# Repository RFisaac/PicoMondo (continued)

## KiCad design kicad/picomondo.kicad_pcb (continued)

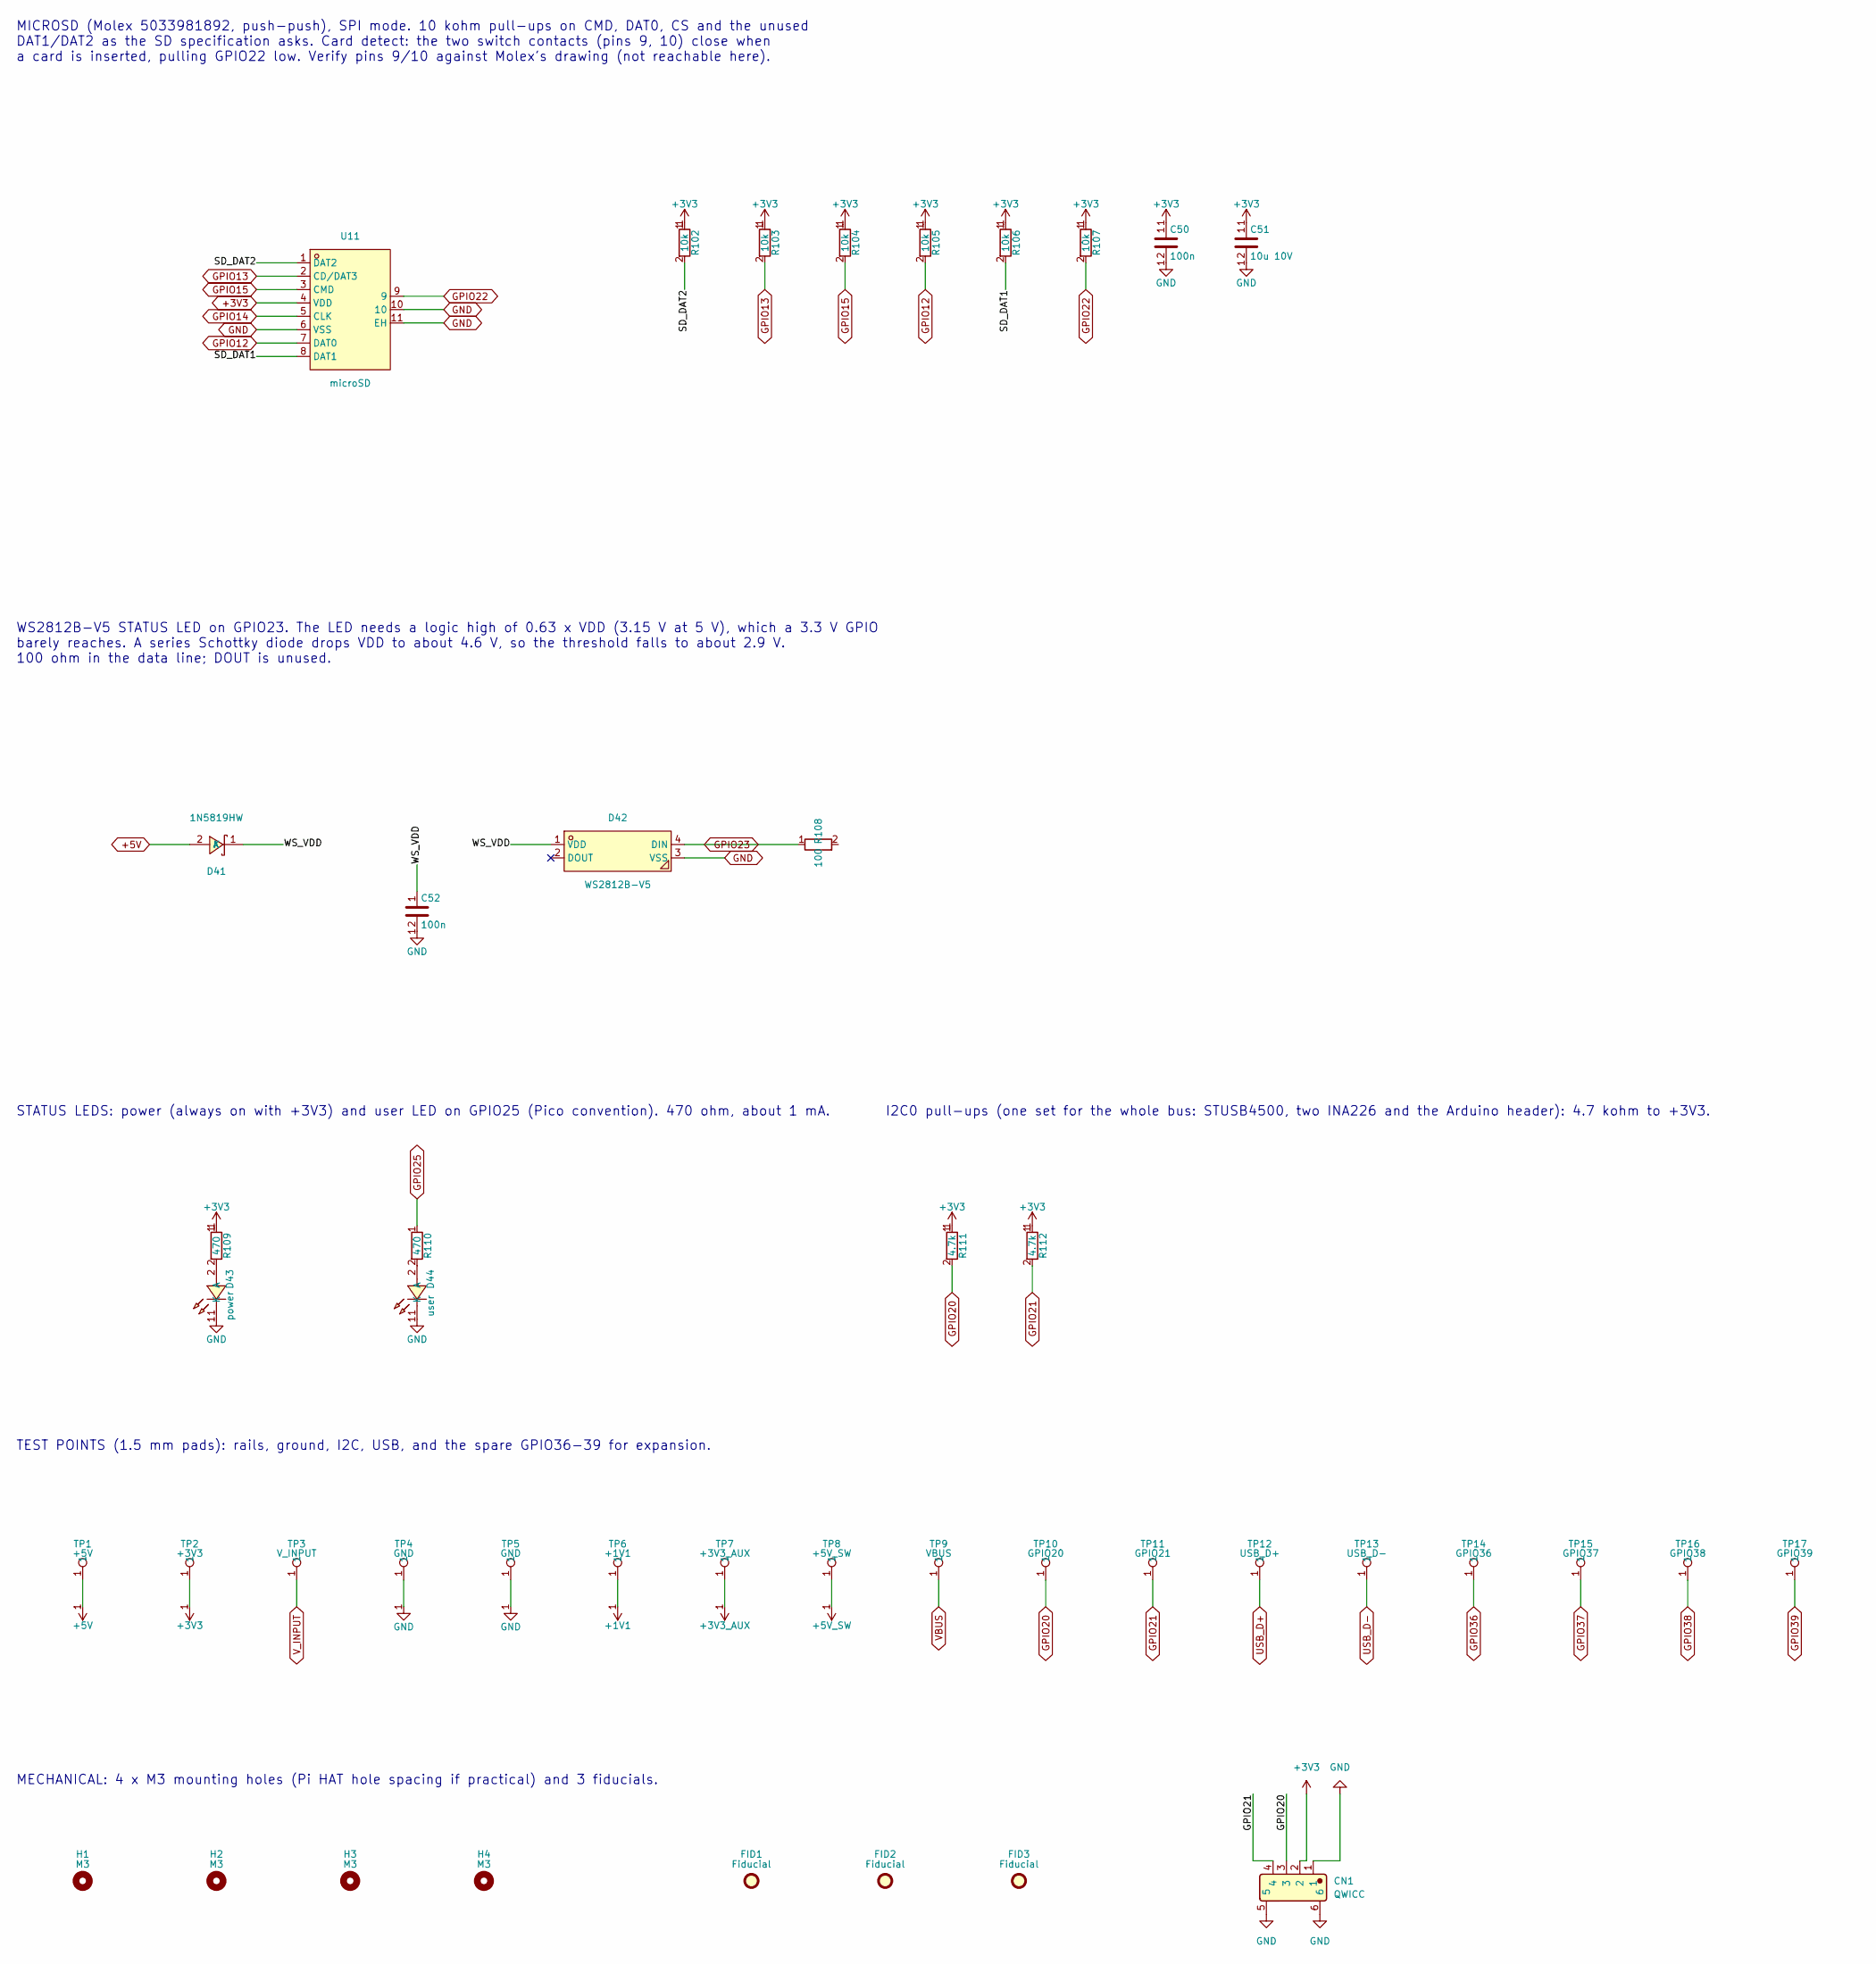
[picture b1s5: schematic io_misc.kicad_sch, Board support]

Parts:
C50, C52: 100n; C_0402_1005Metric; MPN CL05B104KB54PNC; LCSC C307331
C51: 10u 10V; C_0805_2012Metric; MPN CL21A106KAYNNNE; LCSC C15850
CN1: QWICC; XY-SM04B-SRSS-TB; Manufacturer Part XY-SM04B-SRSS-TB; LCSC C51940130
D41: 1N5819HW; SOD-123_L2.7-W1.6-LS3.7-RD; MPN 1N5819HW-7-F; LCSC C82544
D42: WS2812B-V5; LED-SMD_4P-L5.0-W5.0-LS5.4-TL-1; MPN WS2812B-V5/W; LCSC C2874885
D43: power; LED-SMD_L1.0-W0.5-RD_WHITE; MPN LW QH8G-Q2OO-3K5L-1; LCSC C7220928
D44: user; LED-SMD_L1.0-W0.5-RD_WHITE; MPN LW QH8G-Q2OO-3K5L-1; LCSC C7220928
FID1, FID2, FID3: Fiducial; Fiducial_1mm_Mask2mm
H1, H2, H3, H4: M3; MountingHole_3.2mm_M3
R102, R103, R104, R105, R106, R107: 10k; R_0402_1005Metric; MPN 0402WGF1002TCE; LCSC C25744
R108: 100; R_0402_1005Metric; MPN 0402WGF1000TCE; LCSC C25076
R109, R110: 470; R_0402_1005Metric; MPN 0402WGF4700TCE; LCSC C25117
R111, R112: 4.7k; R_0402_1005Metric; MPN 0402WGF4701TCE; LCSC C25900
TP1: +5V; TestPoint_Pad_D1.5mm
TP2: +3V3; TestPoint_Pad_D1.5mm
TP3: V_INPUT; TestPoint_Pad_D1.5mm
TP4, TP5: GND; TestPoint_Pad_D1.5mm
TP6: +1V1; TestPoint_Pad_D1.5mm
TP7: +3V3_AUX; TestPoint_Pad_D1.5mm
TP8: +5V_SW; TestPoint_Pad_D1.5mm
TP9: VBUS; TestPoint_Pad_D1.5mm
TP10: GPIO20; TestPoint_Pad_D1.5mm
TP11: GPIO21; TestPoint_Pad_D1.5mm
TP12: USB_D+; TestPoint_Pad_D1.5mm
TP13: USB_D-; TestPoint_Pad_D1.5mm
TP14: GPIO36; TestPoint_Pad_D1.5mm
TP15: GPIO37; TestPoint_Pad_D1.5mm
TP16: GPIO38; TestPoint_Pad_D1.5mm
TP17: GPIO39; TestPoint_Pad_D1.5mm
U11: microSD; TF-SMD_503398-1892; MPN 5033981892; LCSC C428492

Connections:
+1V1: TP6.1 (1_1); also elsewhere on the board
+3V3: C50.1, C51.1, CN1.2, R102.1, R103.1, R104.1, R105.1, R106.1, R107.1, R109.1, R111.1, R112.1, TP2.1 (1_1), U11.4 (VDD); also elsewhere on the board
+3V3_AUX: TP7.1 (1_1); also elsewhere on the board
+5V: D41.2 (A), TP1.1 (1_1); also elsewhere on the board
+5V_SW: TP8.1 (1_1); also elsewhere on the board
/Board support/SD_DAT1: R106.2, U11.8 (DAT1)
/Board support/SD_DAT2: R102.2, U11.1 (DAT2)
/Board support/WS_VDD: C52.1, D41.1 (K), D42.1 (VDD)
GND: C50.2, C51.2, C52.2, CN1.1, CN1.5, CN1.6, D42.3 (VSS), D43.1 (K), D44.1 (K), TP4.1 (1_1), TP5.1 (1_1), U11.6 (VSS), U11.10, U11.11 (EH); also elsewhere on the board
GPIO12: R105.2, U11.7 (DAT0); also elsewhere on the board
GPIO13: R103.2, U11.2 (CD/DAT3); also elsewhere on the board
GPIO14: U11.5 (CLK); also elsewhere on the board
GPIO15: R104.2, U11.3 (CMD); also elsewhere on the board
GPIO20: CN1.3, R111.2, TP10.1 (1_1); also elsewhere on the board
GPIO21: CN1.4, R112.2, TP11.1 (1_1); also elsewhere on the board
GPIO22: R107.2, U11.9; also elsewhere on the board
GPIO23: D42.4 (DIN), R108.1; also elsewhere on the board
GPIO25: R110.1; also elsewhere on the board
GPIO36: TP14.1 (1_1); also elsewhere on the board
GPIO37: TP15.1 (1_1); also elsewhere on the board
GPIO38: TP16.1 (1_1); also elsewhere on the board
GPIO39: TP17.1 (1_1); also elsewhere on the board
unnamed: D43.2 (A), R109.2
unnamed: D44.2 (A), R110.2
USB_D+: TP12.1 (1_1); also elsewhere on the board
USB_D-: TP13.1 (1_1); also elsewhere on the board
VBUS: TP9.1 (1_1); also elsewhere on the board
V_INPUT: TP3.1 (1_1); also elsewhere on the board

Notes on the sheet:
MECHANICAL: 4 x M3 mounting holes (Pi HAT hole spacing if practical) and 3 fiducials.
I2C0 pull-ups (one set for the whole bus: STUSB4500, two INA226 and the Arduino header): 4.7 kohm to +3V3.
TEST POINTS (1.5 mm pads): rails, ground, I2C, USB, and the spare GPIO36-39 for expansion.
STATUS LEDS: power (always on with +3V3) and user LED on GPIO25 (Pico convention). 470 ohm, about 1 mA.
MICROSD (Molex 5033981892, push-push), SPI mode. 10 kohm pull-ups on CMD, DAT0, CS and the unused DAT1/DAT2 as the SD specification asks. Card detect: the two switch contacts (pins 9, 10) close when a card is inserted, pulling GPIO22 low. Verify pins 9/10 against Molex's drawing (not reachable here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
WS2812B-V5 STATUS LED on GPIO23. The LED needs a logic high of 0.63 x VDD (3.15 V at 5 V), which a 3.3 V GPIO barely reaches. A series Schottky diode drops VDD to about 4.6 V, so the threshold falls to about 2.9 V. 100 ohm in the data line; DOUT is unused.

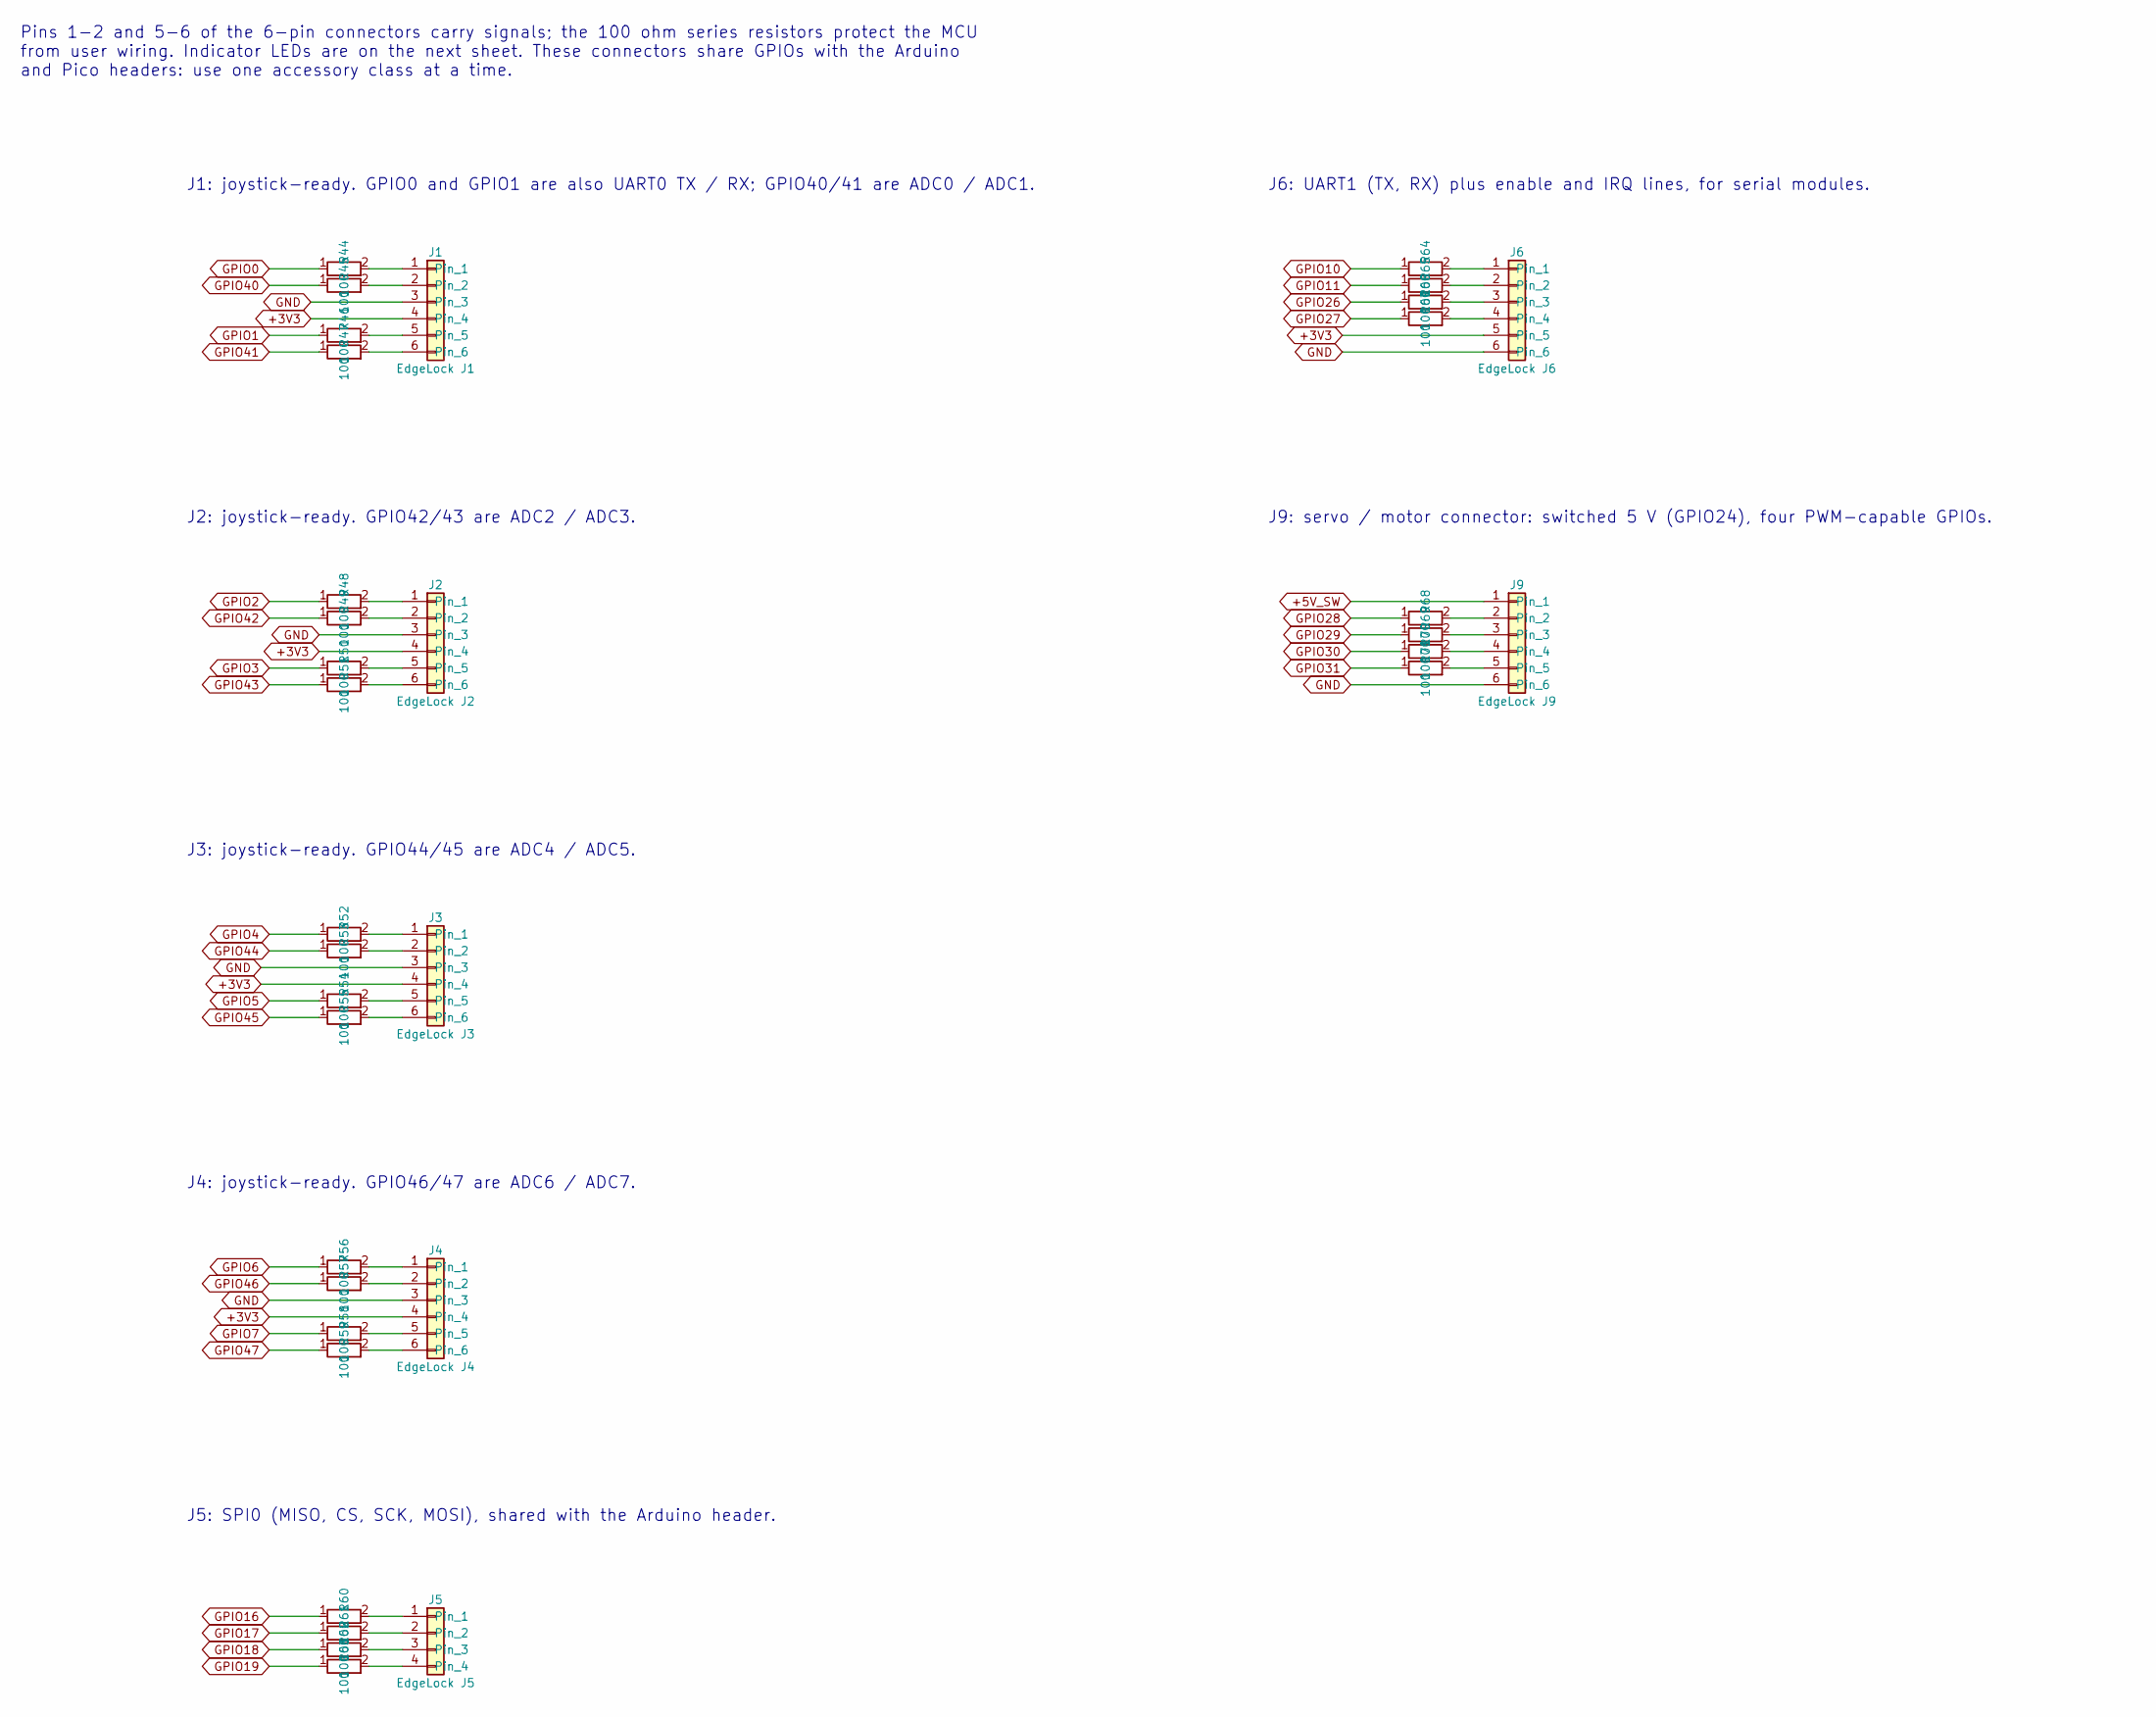
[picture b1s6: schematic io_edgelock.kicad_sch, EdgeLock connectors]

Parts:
J1: EdgeLock J1; EdgeLock_6ckt_Molex2008900106; MPN Molex 2008900106 (mating housing, bough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
J2: EdgeLock J2; EdgeLock_6ckt_Molex2008900106; MPN Molex 2008900106 (mating housing, bough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
J3: EdgeLock J3; EdgeLock_6ckt_Molex2008900106; MPN Molex 2008900106 (mating housing, bough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
J4: EdgeLock J4; EdgeLock_6ckt_Molex2008900106; MPN Molex 2008900106 (mating housing, bough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
J5: EdgeLock J5; EdgeLock_4ckt_Molex2008900104; MPN Molex 2008900104 (mating housing, bough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
J6: EdgeLock J6; EdgeLock_6ckt_Molex2008900106; MPN Molex 2008900106 (mating housing, bough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
J9: EdgeLock J9; EdgeLock_6ckt_Molex2008900106; MPN Molex 2008900106 (mating housing, bough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
R44, R45, R46, R47, R48, R49, R50, R51, R52, R53, R54, R55, R56, R57, R58, R59, R60, R61, R62, R63, R64, R65, R66, R67, R68, R69, R70, R71: 100; R_0402_1005Metric; MPN 0402WGF1000TCE; LCSC C25076

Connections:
+3V3: J1.4, J2.4, J3.4, J4.4, J6.5; also elsewhere on the board
+5V_SW: J9.1; also elsewhere on the board
GND: J1.3, J2.3, J3.3, J4.3, J6.6, J9.6; also elsewhere on the board
GPIO0: R44.1; also elsewhere on the board
GPIO1: R46.1; also elsewhere on the board
GPIO2: R48.1; also elsewhere on the board
GPIO3: R50.1; also elsewhere on the board
GPIO4: R52.1; also elsewhere on the board
GPIO5: R54.1; also elsewhere on the board
GPIO6: R56.1; also elsewhere on the board
GPIO7: R58.1; also elsewhere on the board
GPIO10: R64.1; also elsewhere on the board
GPIO11: R65.1; also elsewhere on the board
GPIO16: R60.1; also elsewhere on the board
GPIO17: R61.1; also elsewhere on the board
GPIO18: R62.1; also elsewhere on the board
GPIO19: R63.1; also elsewhere on the board
GPIO26: R66.1; also elsewhere on the board
GPIO27: R67.1; also elsewhere on the board
GPIO28: R68.1; also elsewhere on the board
GPIO29: R69.1; also elsewhere on the board
GPIO30: R70.1; also elsewhere on the board
GPIO31: R71.1; also elsewhere on the board
GPIO40: R45.1; also elsewhere on the board
GPIO41: R47.1; also elsewhere on the board
GPIO42: R49.1; also elsewhere on the board
GPIO43: R51.1; also elsewhere on the board
GPIO44: R53.1; also elsewhere on the board
GPIO45: R55.1; also elsewhere on the board
GPIO46: R57.1; also elsewhere on the board
GPIO47: R59.1; also elsewhere on the board
unnamed: J1.1, R44.2
unnamed: J1.2, R45.2
unnamed: J1.5, R46.2
unnamed: J1.6, R47.2
unnamed: J2.1, R48.2
unnamed: J2.2, R49.2
unnamed: J2.5, R50.2
unnamed: J2.6, R51.2
unnamed: J3.1, R52.2
unnamed: J3.2, R53.2
unnamed: J3.5, R54.2
unnamed: J3.6, R55.2
unnamed: J4.1, R56.2
unnamed: J4.2, R57.2
unnamed: J4.5, R58.2
unnamed: J4.6, R59.2
unnamed: J5.1, R60.2
unnamed: J5.2, R61.2
unnamed: J5.3, R62.2
unnamed: J5.4, R63.2
unnamed: J6.1, R64.2
unnamed: J6.2, R65.2
unnamed: J6.3, R66.2
unnamed: J6.4, R67.2
unnamed: J9.2, R68.2
unnamed: J9.3, R69.2
unnamed: J9.4, R70.2
unnamed: J9.5, R71.2

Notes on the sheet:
J3: joystick-ready. GPIO44/45 are ADC4 / ADC5.
J2: joystick-ready. GPIO42/43 are ADC2 / ADC3.
J6: UART1 (TX, RX) plus enable and IRQ lines, for serial modules.
J9: servo / motor connector: switched 5 V (GPIO24), four PWM-capable GPIOs.
J4: joystick-ready. GPIO46/47 are ADC6 / ADC7.
J5: SPI0 (MISO, CS, SCK, MOSI), shared with the Arduino header.
Pins 1-2 and 5-6 of the 6-pin connectors carry signals; the 100 ohm series resistors protect the MCU from user wiring. Indicator LEDs are on the next sheet. These connectors share GPIOs with the Arduino and Pico headers: use one accessory class at a time.
J1: joystick-ready. GPIO0 and GPIO1 are also UART0 TX / RX; GPIO40/41 are ADC0 / ADC1.

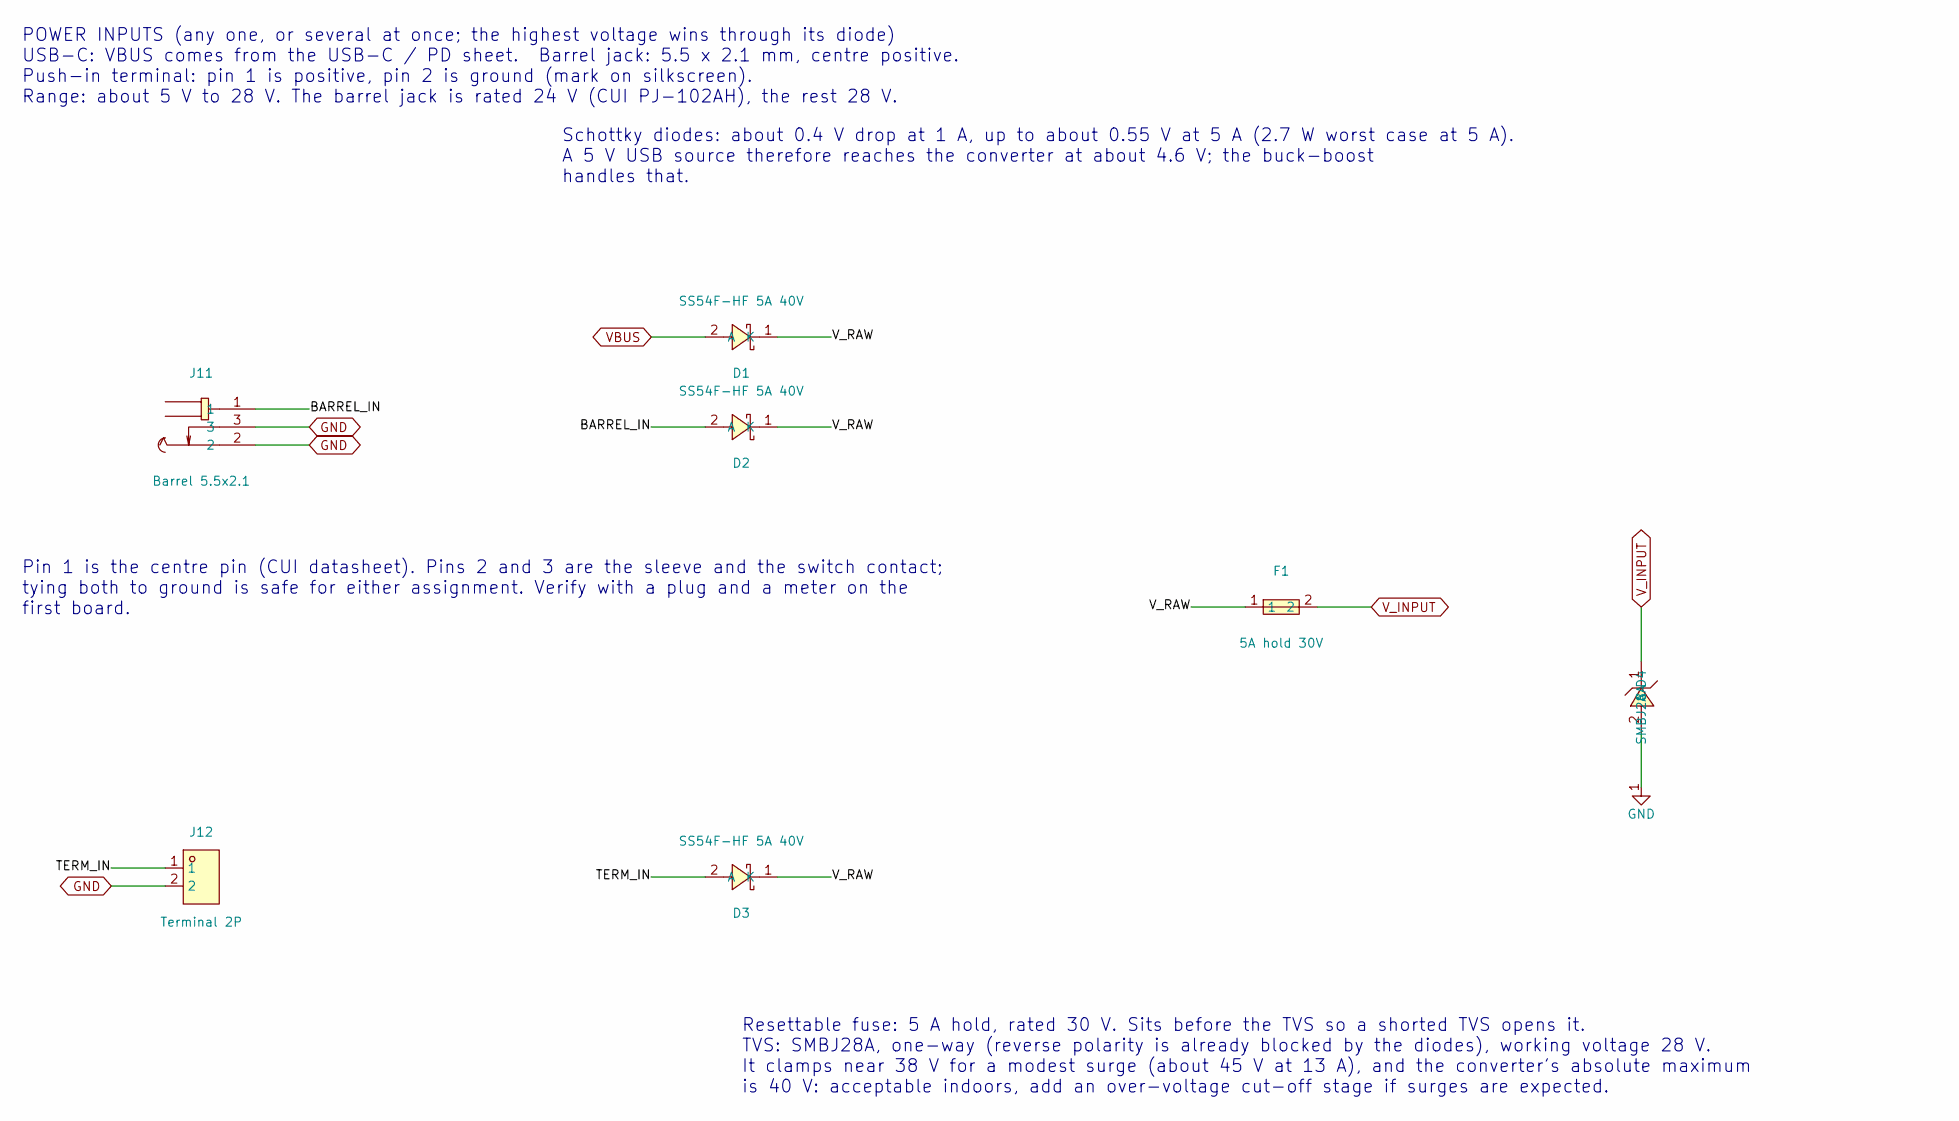
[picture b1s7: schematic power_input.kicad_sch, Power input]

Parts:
D1, D2, D3: SS54F-HF 5A 40V; DO-214AD_L4.0-W2.5-LS4.8-FD; MPN SS54F-HF; LCSC C5142774
D4: SMBJ28A; SMB_L4.6-W3.6-LS5.3-RD; MPN SMBJ28A; LCSC C178227
F1: 5A hold 30V; F2920; MPN 2920L500/30GR; LCSC C19078763
J11: Barrel 5.5x2.1; DC-IN-TH_PJ-102AH; MPN PJ-102AH; LCSC C3096093
J12: Terminal 2P; CONN-SMD_2060-452; MPN 2060-452/998-404; LCSC C2765055

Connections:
/Power input/BARREL_IN: D2.2 (A), J11.1
/Power input/TERM_IN: D3.2 (A), J12.1
/Power input/V_RAW: D1.1 (K), D2.1 (K), D3.1 (K), F1.1
GND: D4.2 (A), J11.2, J11.3, J12.2; also elsewhere on the board
VBUS: D1.2 (A); also elsewhere on the board
V_INPUT: D4.1 (C), F1.2; also elsewhere on the board

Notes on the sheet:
POWER INPUTS (any one, or several at once; the highest voltage wins through its diode) USB-C: VBUS comes from the USB-C / PD sheet. Barrel jack: 5.5 x 2.1 mm, centre positive. Push-in terminal: pin 1 is positive, pin 2 is ground (mark on silkscreen). Range: about 5 V to 28 V. The barrel jack is rat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
Pin 1 is the centre pin (CUI datasheet). Pins 2 and 3 are the sleeve and the switch contact; tying both to ground is safe for either assignment. Verify with a plug and a meter on the first board.
Schottky diodes: about 0.4 V drop at 1 A, up to about 0.55 V at 5 A (2.7 W worst case at 5 A). A 5 V USB source therefore reaches the converter at about 4.6 V; the buck-boost handles that.
Resettable fuse: 5 A hold, rated 30 V. Sits before the TVS so a shorted TVS opens it. TVS: SMBJ28A, one-way (reverse polarity is already blocked by the diodes), working voltage 28 V. It clamps near 38 V for a modest surge (about 45 V at 13 A), and the converter's absolute maximum is 40 V: acceptabl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

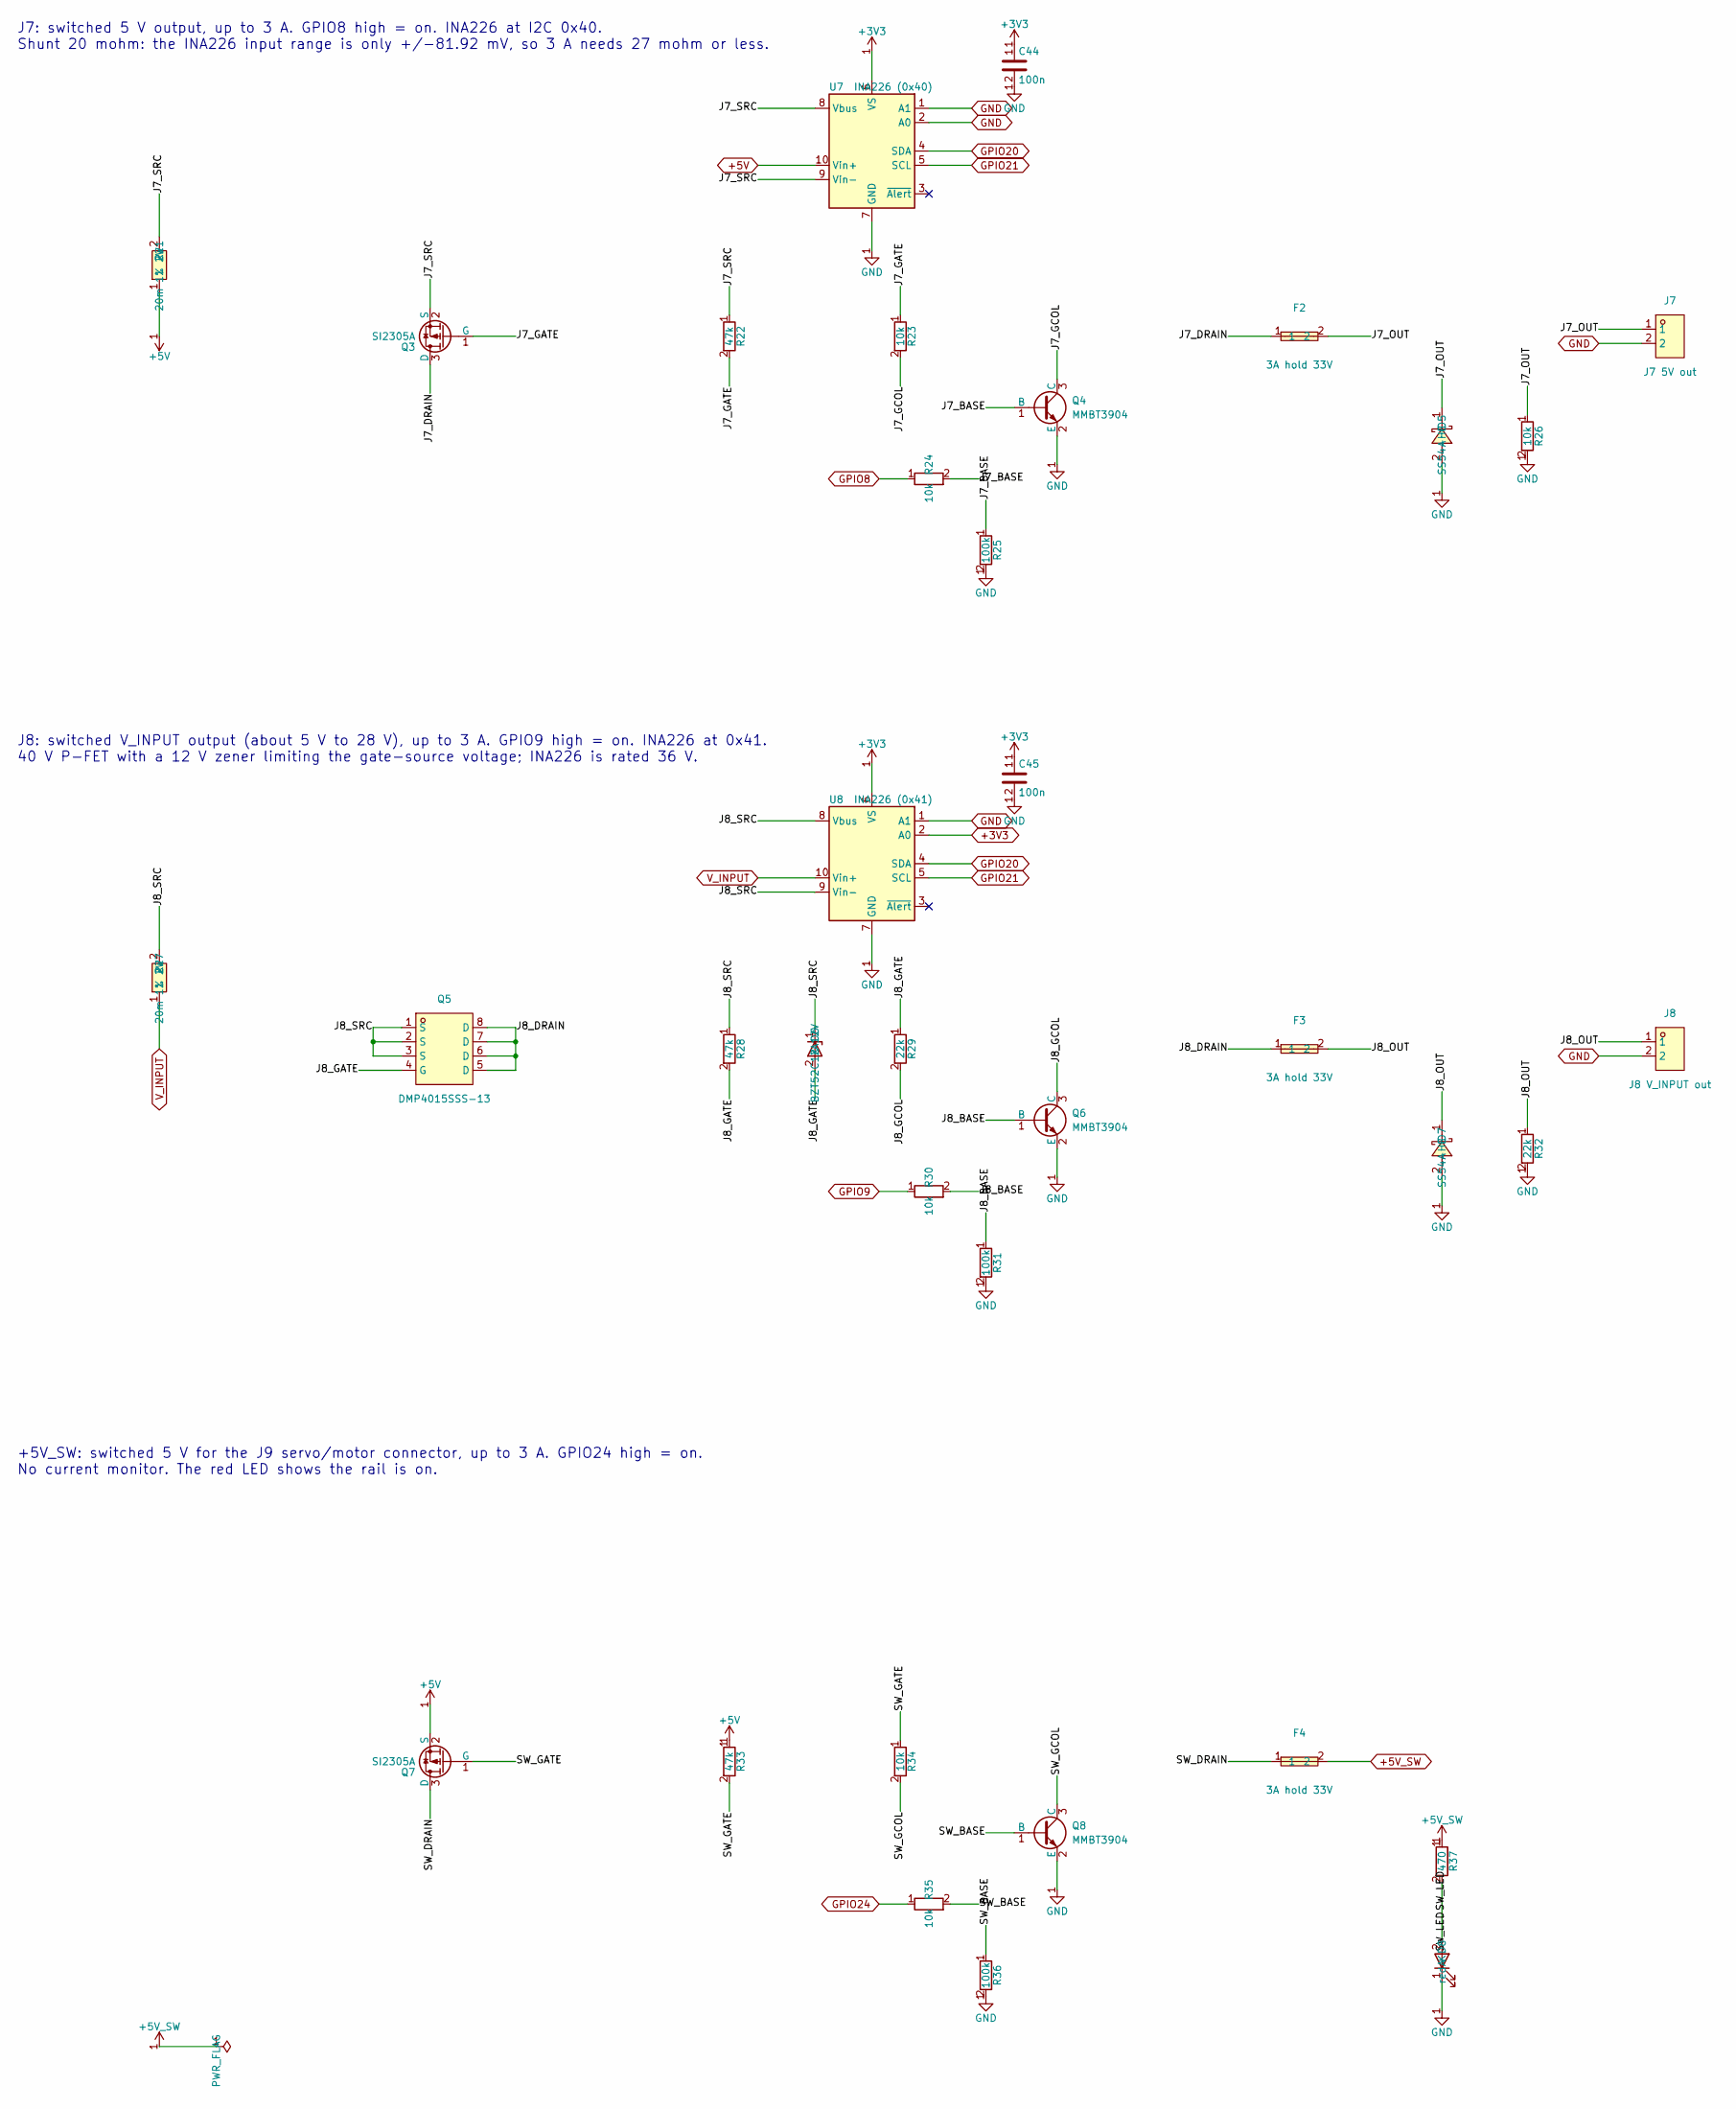
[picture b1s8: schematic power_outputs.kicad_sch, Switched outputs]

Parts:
C44, C45: 100n; C_0402_1005Metric; MPN CL05B104KB54PNC; LCSC C307331
D5, D7: SS54-HF; SMA_L4.3-W2.5-LS5.0-RD; MPN SS54; LCSC C22452
D6: BZT52C12 12V; D_SOD-123; MPN BZT52C12-13-F; LCSC C177013
D8: red; LED_0603_1608Metric; MPN KT-0603R; LCSC C2286
F2, F3, F4: 3A hold 33V; F1812; MPN 1812L300/33GR; LCSC C54300298
J7: J7 5V out; CONN-TH_P5.00_KF301-5.0-2P; MPN KF301-5.0-2P; LCSC C474881
J8: J8 V_INPUT out; CONN-TH_P5.00_KF301-5.0-2P; MPN KF301-5.0-2P; LCSC C474881
Q3, Q7: SI2305A; SOT-23; MPN SI2305A; LCSC C347488
Q4, Q6, Q8: MMBT3904; SOT-23; MPN MMBT3904LT1G; LCSC C81464
Q5: DMP4015SSS-13; SO-8_L4.9-W3.9-P1.27-LS5.9-BL; MPN DMP4015SSS-13; LCSC C508210
R21, R27: 20m 1% 2W; R2512; MPN GX2512-2W-20mR-1%; LCSC C500720
R22, R28, R33: 47k; R_0402_1005Metric; MPN 0402WGF4702TCE; LCSC C25792
R23, R24, R26, R30, R34, R35: 10k; R_0402_1005Metric; MPN 0402WGF1002TCE; LCSC C25744
R25, R31, R36: 100k; R_0402_1005Metric; MPN 0402WGF1003TCE; LCSC C25741
R29: 22k; R_0603_1608Metric; MPN 0603WAF2202T5E; LCSC C31850
R32: 22k; R_0402_1005Metric; MPN 0402WGF2202TCE; LCSC C25768
R37: 470; R_0402_1005Metric; MPN 0402WGF4700TCE; LCSC C25117
U7: INA226 (0x40); MSOP-10_3x3mm_P0.5mm; MPN INA226AIDGSR; LCSC C49851
U8: INA226 (0x41); MSOP-10_3x3mm_P0.5mm; MPN INA226AIDGSR; LCSC C49851

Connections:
+3V3: C44.1, C45.1, U7.6 (VS), U8.2 (A0), U8.6 (VS); also elsewhere on the board
+5V: Q7.2 (S), R21.1, R33.1, U7.10 (Vin+); also elsewhere on the board
+5V_SW: F4.2, R37.1; also elsewhere on the board
/Switched outputs/J7_BASE: Q4.1 (B), R24.2, R25.1
/Switched outputs/J7_DRAIN: F2.1, Q3.3 (D)
/Switched outputs/J7_GATE: Q3.1 (G), R22.2, R23.1
/Switched outputs/J7_GCOL: Q4.3 (C), R23.2
/Switched outputs/J7_OUT: D5.1 (C), F2.2, J7.1, R26.1
/Switched outputs/J7_SRC: Q3.2 (S), R21.2, R22.1, U7.8 (Vbus), U7.9 (Vin-)
/Switched outputs/J8_BASE: Q6.1 (B), R30.2, R31.1
/Switched outputs/J8_DRAIN: F3.1, Q5.5 (D), Q5.6 (D), Q5.7 (D), Q5.8 (D)
/Switched outputs/J8_GATE: D6.2 (A), Q5.4 (G), R28.2, R29.1
/Switched outputs/J8_GCOL: Q6.3 (C), R29.2
/Switched outputs/J8_OUT: D7.1 (C), F3.2, J8.1, R32.1
/Switched outputs/J8_SRC: D6.1 (K), Q5.1 (S), Q5.2 (S), Q5.3 (S), R27.2, R28.1, U8.8 (Vbus), U8.9 (Vin-)
/Switched outputs/SW_BASE: Q8.1 (B), R35.2, R36.1
/Switched outputs/SW_DRAIN: F4.1, Q7.3 (D)
/Switched outputs/SW_GATE: Q7.1 (G), R33.2, R34.1
/Switched outputs/SW_GCOL: Q8.3 (C), R34.2
/Switched outputs/SW_LED: D8.2 (A), R37.2
GND: C44.2, C45.2, D5.2 (A), D7.2 (A), D8.1 (K), J7.2, J8.2, Q4.2 (E), Q6.2 (E), Q8.2 (E), R25.2, R26.2, R31.2, R32.2, R36.2, U7.1 (A1), U7.2 (A0), U7.7 (GND), U8.1 (A1), U8.7 (GND); also elsewhere on the board
GPIO8: R24.1; also elsewhere on the board
GPIO9: R30.1; also elsewhere on the board
GPIO20: U7.4 (SDA), U8.4 (SDA); also elsewhere on the board
GPIO21: U7.5 (SCL), U8.5 (SCL); also elsewhere on the board
GPIO24: R35.1; also elsewhere on the board
V_INPUT: R27.1, U8.10 (Vin+); also elsewhere on the board

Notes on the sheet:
+5V_SW: switched 5 V for the J9 servo/motor connector, up to 3 A. GPIO24 high = on. No current monitor. The red LED shows the rail is on.
J7: switched 5 V output, up to 3 A. GPIO8 high = on. INA226 at I2C 0x40. Shunt 20 mohm: the INA226 input range is only +/-81.92 mV, so 3 A needs 27 mohm or less.
J8: switched V_INPUT output (about 5 V to 28 V), up to 3 A. GPIO9 high = on. INA226 at 0x41. 40 V P-FET with a 12 V zener limiting the gate-source voltage; INA226 is rated 36 V.
